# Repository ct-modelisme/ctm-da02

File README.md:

# CTM-DA02: Blacksmith environment command

The CTM-DA02 is a blacksmith electronic controller for modelrailway projects.
This electronic card is compatible with DCC & AC/DC train layouts.

## Licenses

The hardware is released under OpenHardware principes, and the software under OpenSource principes.

 - Hardware (PCB): [Creative Commons Attribution-ShareAlike 4.0 International License](http://creativecommons.org/licenses/by-sa/4.0/)
 - Software (Firmware): [GNU General Public License v3](https://www.gnu.org/licenses/)

## Current releases

 - Hardware (PCB): version 1.0
 - Software (Firmware): version 1.0

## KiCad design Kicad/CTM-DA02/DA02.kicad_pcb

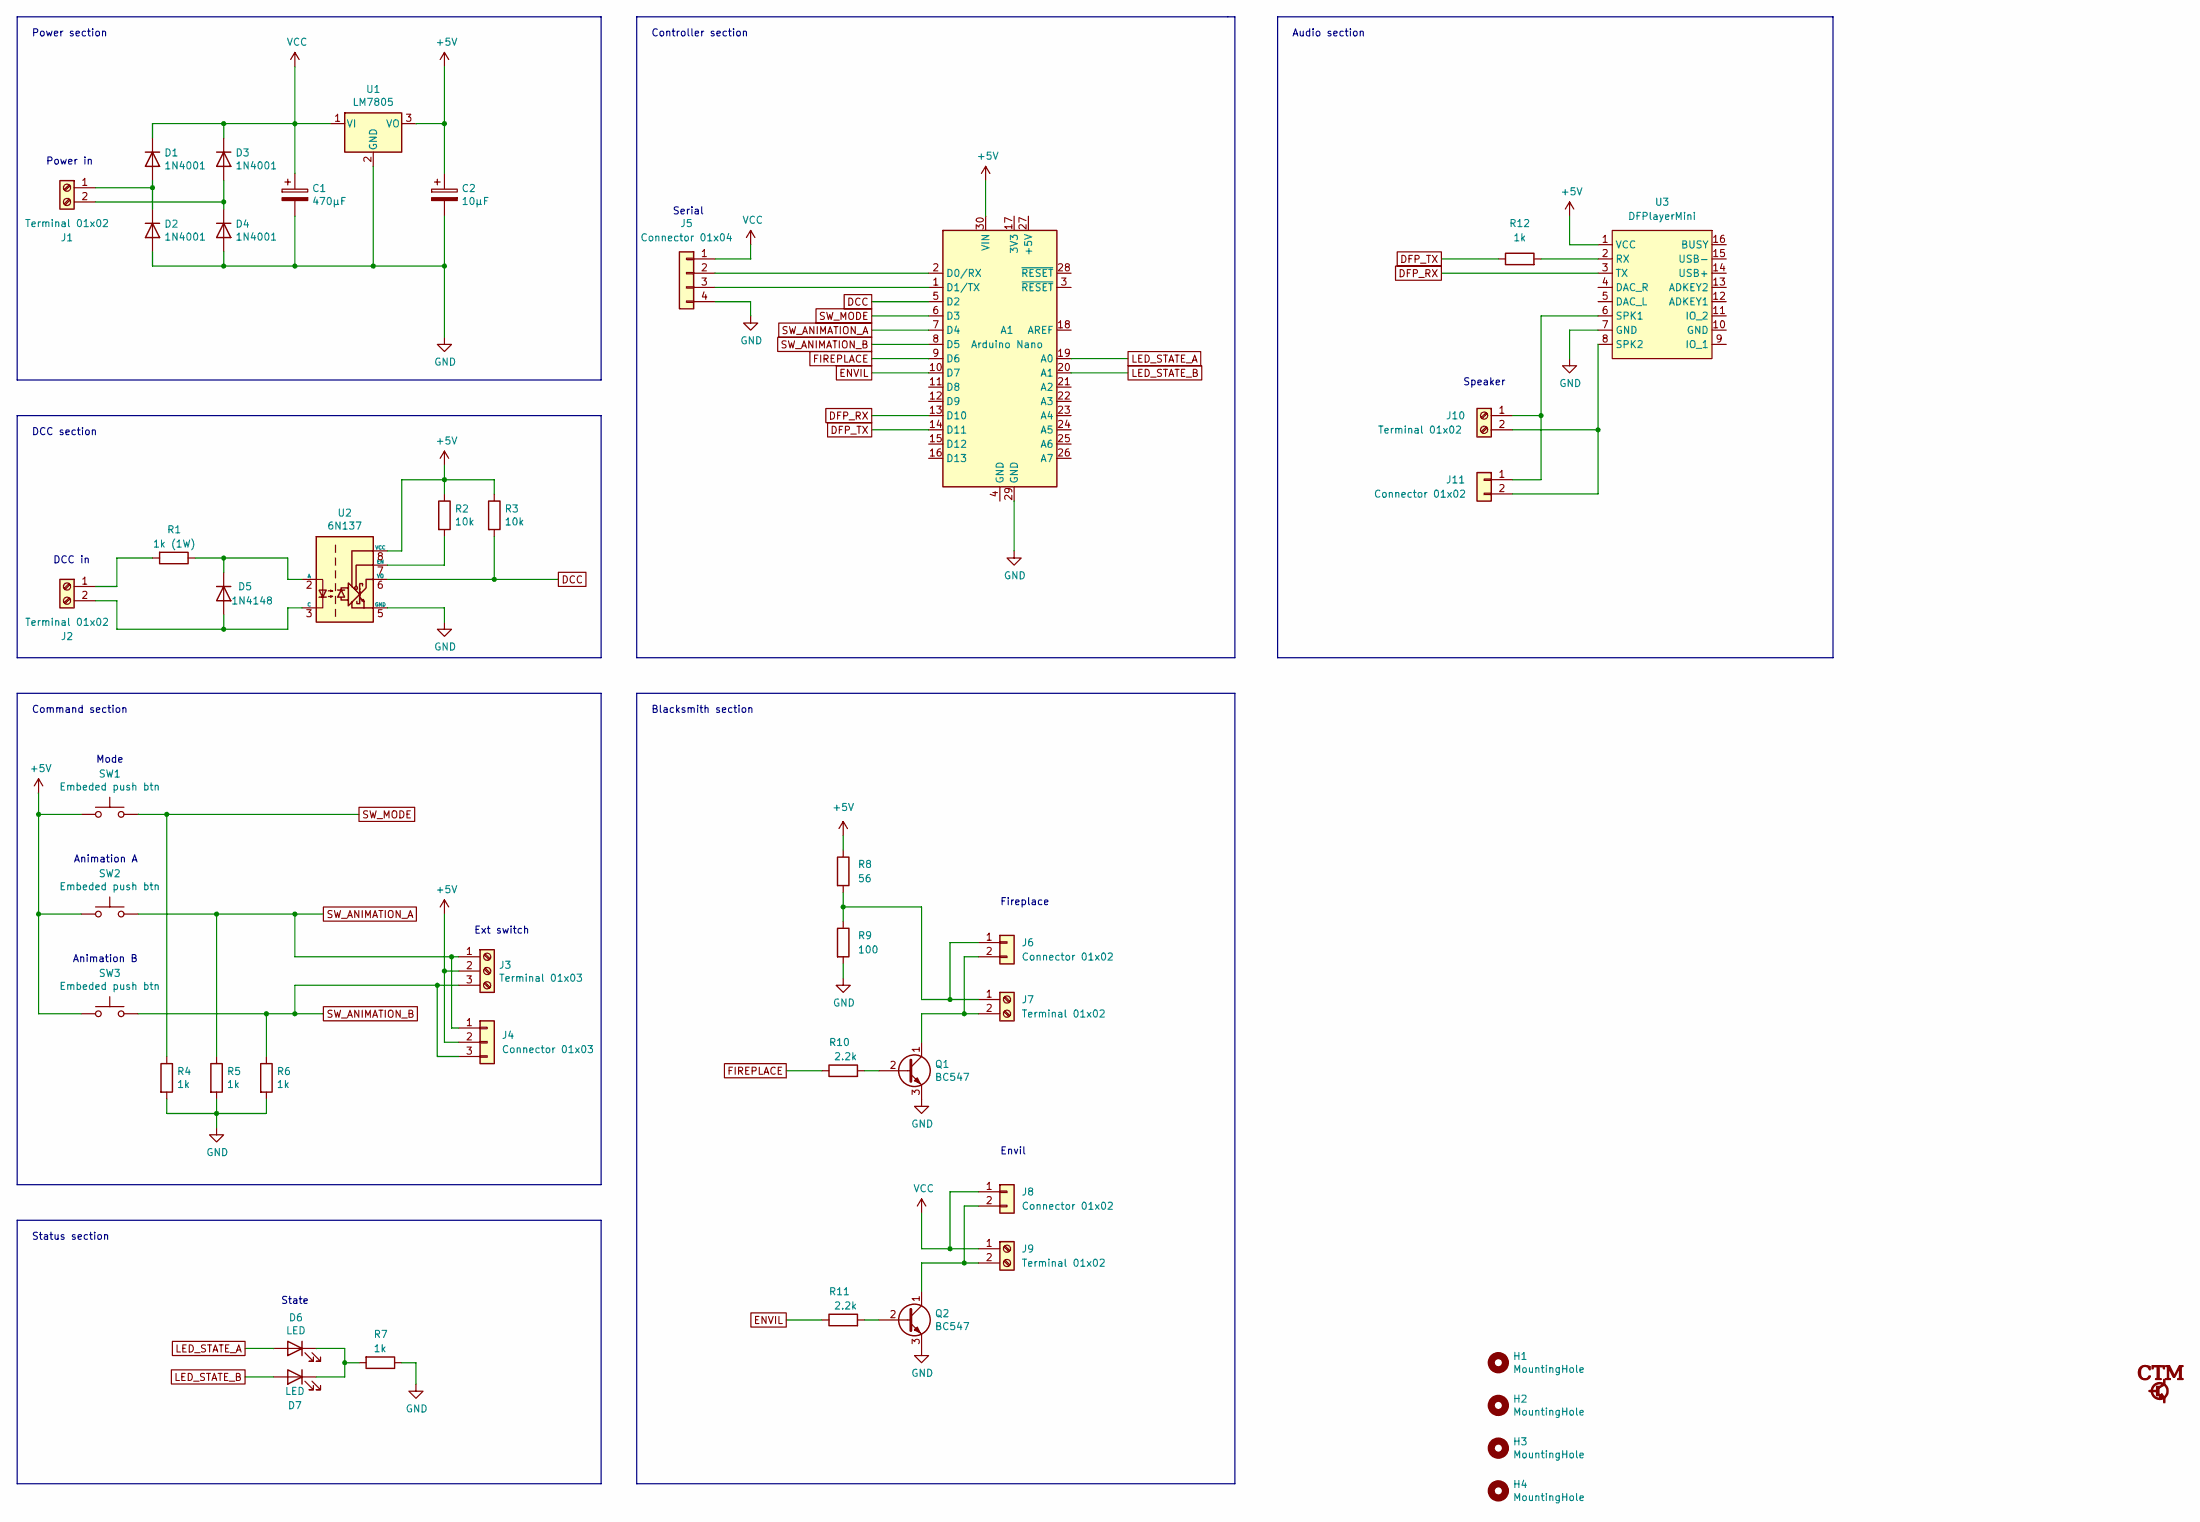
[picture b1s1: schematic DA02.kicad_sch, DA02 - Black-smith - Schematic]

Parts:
A1: Arduino Nano; Arduino_Nano
C1: 470µF; CP_Radial_D10.0mm_P5.00mm
C2: 10µF; CP_Radial_D6.3mm_P2.50mm
D1, D2, D3, D4: 1N4001; D_DO-41_SOD81_P10.16mm_Horizontal
D5: 1N4148; D_DO-35_SOD27_P7.62mm_Horizontal
D6, D7: LED; LED_D3.0mm
H1, H2, H3, H4: MountingHole; MountingHole_3.2mm_M3
J1, J2, J7, J9, J10: Terminal 01x02; TerminalBlock_bornier-2_P5.08mm
J3: Terminal 01x03; TerminalBlock_bornier-3_P5.08mm
J4: Connector 01x03; PinHeader_1x03_P2.54mm_Vertical
J5: Connector 01x04; PinHeader_1x04_P2.54mm_Vertical
J6, J8, J11: Connector 01x02; PinHeader_1x02_P2.54mm_Vertical
Q1, Q2: BC547; TO-92_Inline
R1: 1k (1W); R_Axial_DIN0309_L9.0mm_D3.2mm_P12.70mm_Horizontal
R2, R3: 10k; R_Axial_DIN0207_L6.3mm_D2.5mm_P10.16mm_Horizontal
R4, R5, R6, R7, R12: 1k; R_Axial_DIN0207_L6.3mm_D2.5mm_P10.16mm_Horizontal
R8: 56; R_Axial_DIN0207_L6.3mm_D2.5mm_P10.16mm_Horizontal
R9: 100; R_Axial_DIN0207_L6.3mm_D2.5mm_P10.16mm_Horizontal
R10, R11: 2.2k; R_Axial_DIN0207_L6.3mm_D2.5mm_P10.16mm_Horizontal
SW1, SW2, SW3: Embeded push btn; SW_PUSH_6mm
U1: LM7805; TO-220-3_Vertical
U2: 6N137; DIP-8_W7.62mm
U3: DFPlayerMini; DFRobot_DFPlayerMini_DFR0299

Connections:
+5V: A1.30 (VIN), C2.1, J3.2, J4.2, R2.1, R3.1, R8.1, SW1.1, SW2.1, SW3.1, U1.3 (VO), U2.8 (VCC), U3.1 (VCC)
DCC: A1.5 (D2), R3.2, U2.6 (VO)
DFP_RX: A1.13 (D10), U3.3 (TX)
DFP_TX: A1.14 (D11), R12.1
ENVIL: A1.10 (D7), R11.1
FIREPLACE: A1.9 (D6), R10.1
GND: A1.29 (GND), C1.2, C2.2, D2.2 (A), D4.2 (A), J5.4, Q1.3 (E), Q2.3 (E), R4.2, R5.2, R6.2, R7.1, R9.2, U1.2 (GND), U2.5 (GND), U3.7 (GND)
LED_STATE_A: A1.19 (A0), D6.2 (A)
LED_STATE_B: A1.20 (A1), D7.2 (A)
unnamed: A1.1 (D1/TX), J5.3
unnamed: A1.2 (D0/RX), J5.2
unnamed: D1.2 (A), D2.1 (K), J1.1
unnamed: D3.2 (A), D4.1 (K), J1.2
unnamed: D5.1 (K), R1.1, U2.2 (A)
unnamed: D5.2 (A), J2.2, U2.3 (C)
unnamed: D6.1 (K), D7.1 (K), R7.2
unnamed: J2.1, R1.2
unnamed: J6.1, J7.1, R8.2, R9.1
unnamed: J6.2, J7.2, Q1.1 (C)
unnamed: J8.2, J9.2, Q2.1 (C)
unnamed: J10.1, J11.1, U3.6 (SPK1)
unnamed: J10.2, J11.2, U3.8 (SPK2)
unnamed: Q1.2 (B), R10.2
unnamed: Q2.2 (B), R11.2
unnamed: R2.2, U2.7 (EN)
unnamed: R12.2, U3.2 (RX)
SW_ANIMATION_A: A1.7 (D4), J3.1, J4.1, R5.1, SW2.2
SW_ANIMATION_B: A1.8 (D5), J3.3, J4.3, R6.1, SW3.2
SW_MODE: A1.6 (D3), R4.1, SW1.2
VCC: C1.1, D1.1 (K), D3.1 (K), J5.1, J8.1, J9.1, U1.1 (VI)

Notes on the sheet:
Audio section
Command section
Status section
Power section
Animation B
Power in
Mode
Controller section
Fireplace
State
Envil
DCC in
Blacksmith section
Ext switch
Serial
Speaker
Animation A
DCC section

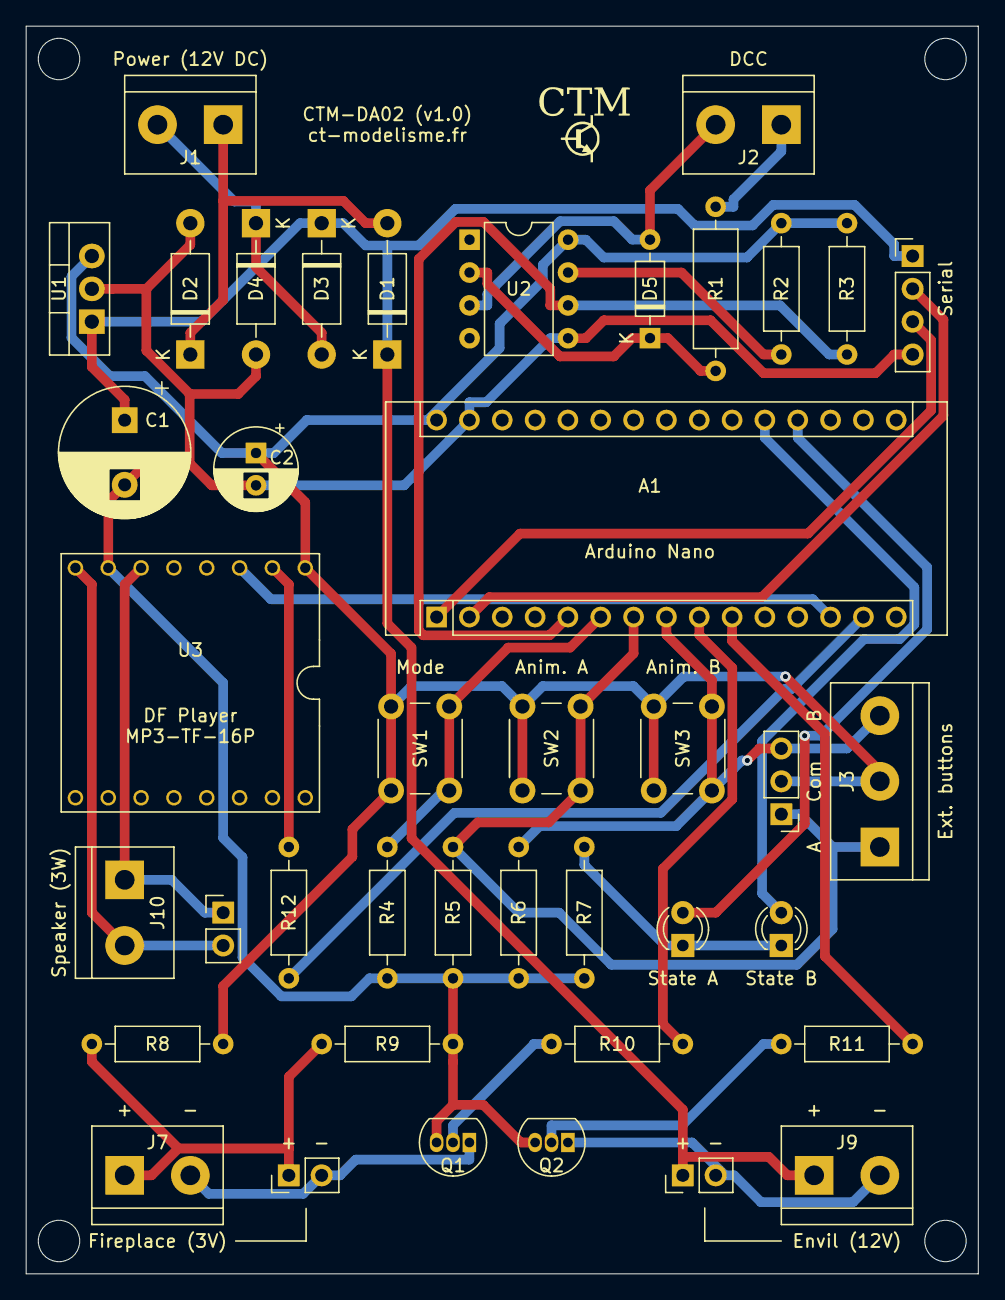
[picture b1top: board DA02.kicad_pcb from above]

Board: 2 copper layers, 73.7 x 96.5 mm, 45 parts (0 on the bottom side), 30 nets.

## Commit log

2024-02-24 Release first PCB version
2024-02-24 Release first firmware version
2024-02-24 Release first documentation version
